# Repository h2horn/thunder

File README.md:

Lightning Thunder
=================

Controlling [LPD8806](https://www.adafruit.com/products/306) based LED Strips over Network.

* control up to 4 LPD8806 based LED Strips
* simple UDP Protocol

Components
----------

Based on:

* [ATxmega16A4](http://www.atmel.com/Images/Atmel-8331-8-and-16-bit-AVR-Microcontroller-XMEGA-AU_Manual.pdf) - Low power, high performance 8/16-bit AVR microcontroller
* [ENC28J60](http://ww1.microchip.com/downloads/en/DeviceDoc/39662e.pdf) - Microchip 10Mbit Ethernet controller with SPI interface

Protocol
--------

`Thunder` recieves UDP data containing the raw LPD8806 data for each Strip
on seperate UDP Ports (50000-50003). It forwards the data directly over SPI, without any checking or modification.

The Host has full control and has to calculate the correct order and
color ordering (RBG -> RGB), etc...

Result
------

LICENSE
-------

Released under the [MIT](http://opensource.org/licenses/MIT) License.
Based on the [Open Source Hardware Definition v1.0](http://www.oshwa.org/definition/).

See the respective source code files for varying Licenses.

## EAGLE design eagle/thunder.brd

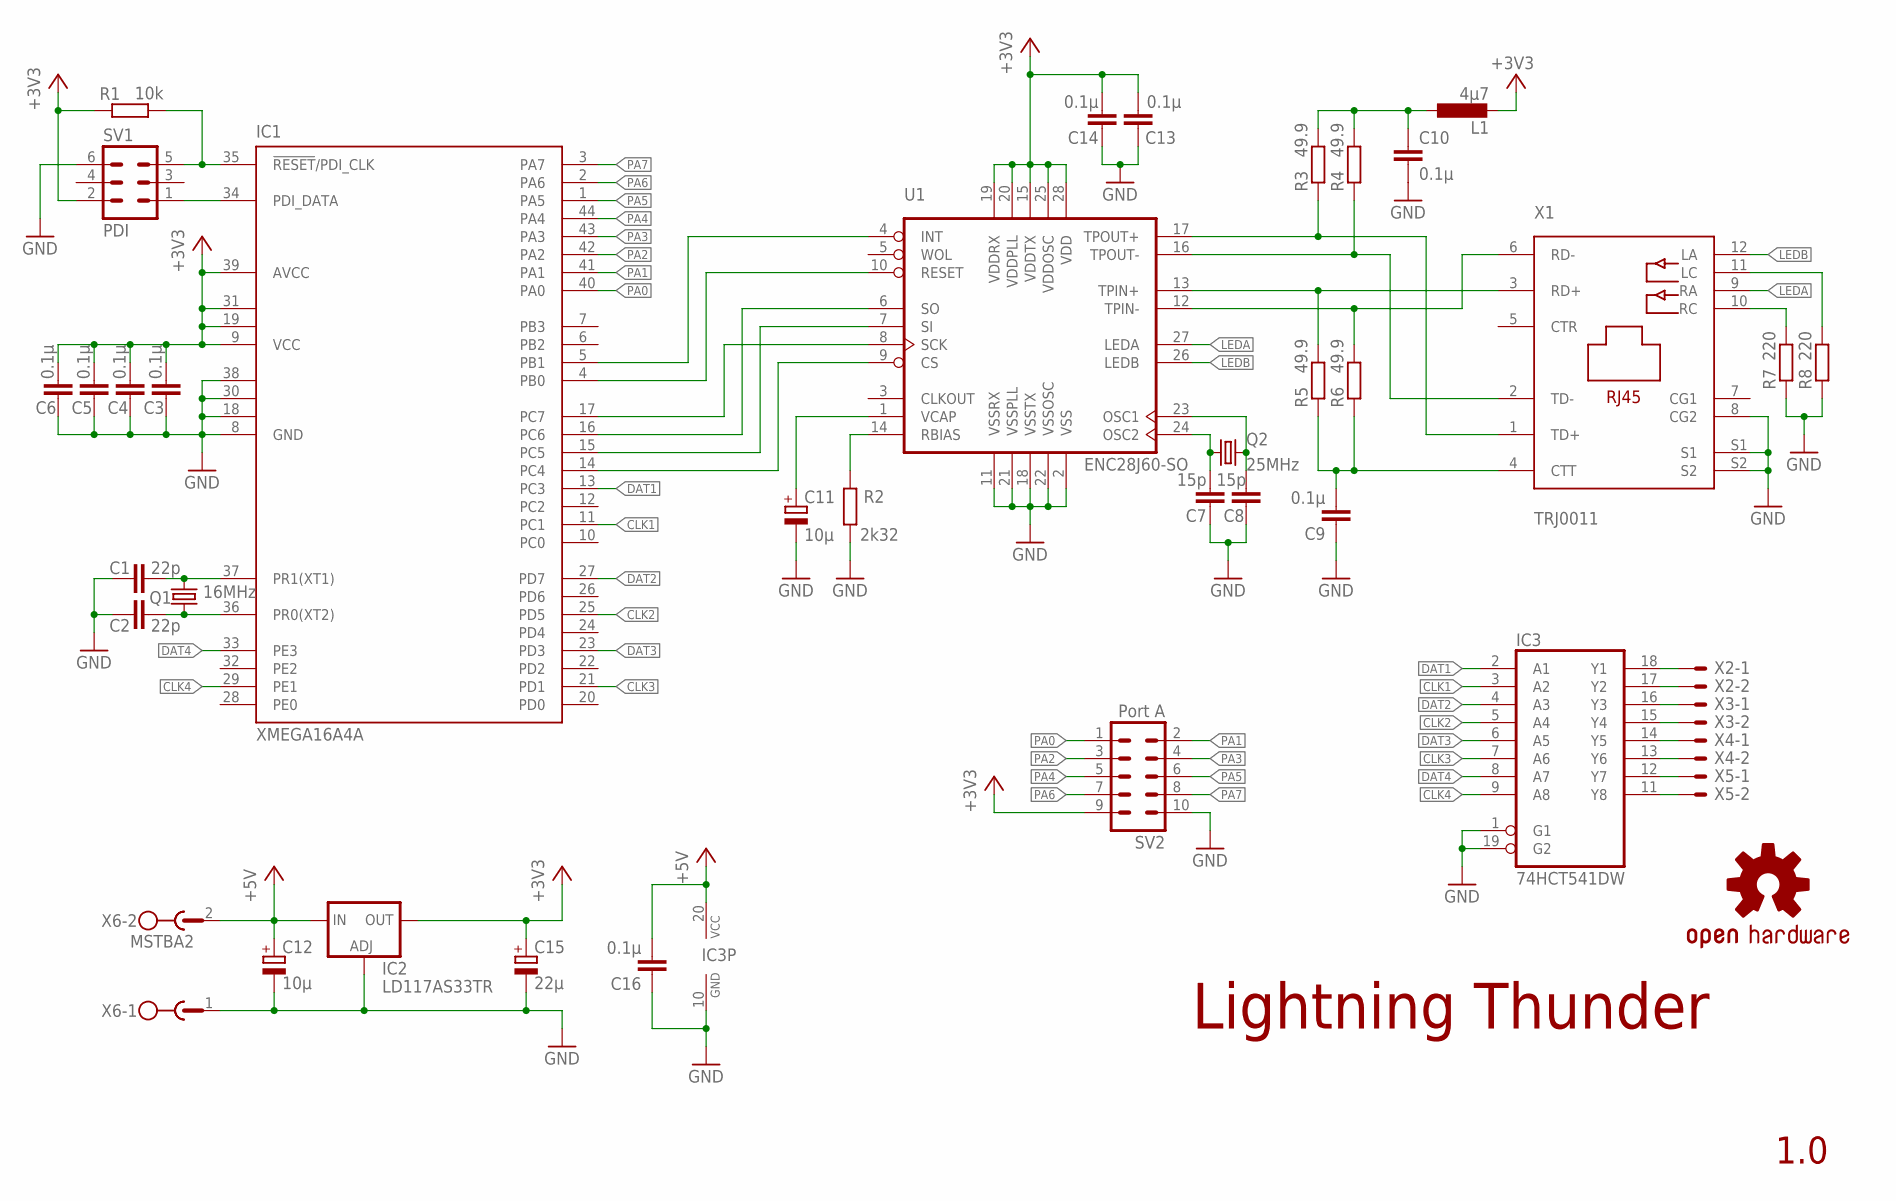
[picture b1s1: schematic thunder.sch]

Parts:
C1, C2: 22p; C0805
C3, C4, C5, C6, C9, C10, C13, C14, C16: 0.1µ; C0805
C7, C8: 15p; C0805
C11, C12: 10µ; B/3528-21R
C15: 22µ; B/3528-21R
IC1: XMEGA16A4A; TQFP44
IC2: LD117AS33TR; SOT223
IC3: 74HCT541DW; SO20W
L1: 4µ7; L3225M
LOGO1: OSHW-LOGOS; OSHW-LOGO-S
Q1: 16MHz; HC49U-V
Q2: 25MHz; HC49U-V
R1: 10k; R0805
R2: 2k32; R0805
R3, R4, R5, R6: 49.9; R0805
R7, R8: 220; R0805
SV1: PDI; ML6
SV2: Port A; MA05-2
U1: ENC28J60-SO; SO28W
X1: TRJ0011
X2, X3, X4, X5: AKL18X-02W; AKL182-02
X6: MSTBA2

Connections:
+3V3: C3.2, C4.2, C5.2, C6.2, C13.2, C14.2, C15.+, IC1.9 (VCC), IC1.19 (VCC1), IC1.31 (VCC2), IC1.39 (AVCC), IC2.4 (OUT), L1.2, R1.2, SV1.2, SV2.9, U1.15 (VDDTX), U1.19 (VDDRX), U1.20 (VDDPLL), U1.25 (VDDOSC), U1.28 (VDD)
+5V: C12.+, C16.2, IC2.3 (IN), IC3.20 (VCC), X6.2
CLK1: IC1.11 (PC1), IC3.3 (A2)
CLK2: IC1.25 (PD5), IC3.5 (A4)
CLK3: IC1.21 (PD1), IC3.7 (A6)
CLK4: IC1.29 (PE1), IC3.9 (A8)
DAT1: IC1.13 (PC3), IC3.2 (A1)
DAT2: IC1.27 (PD7), IC3.4 (A3)
DAT3: IC1.23 (PD3), IC3.6 (A5)
DAT4: IC1.33 (PE3), IC3.8 (A7)
GND: C1.1, C2.1, C3.1, C4.1, C5.1, C6.1, C7.1, C8.1, C9.1, C10.2, C11.-, C12.-, C13.1, C14.1, C15.-, C16.1, IC1.8 (GND), IC1.18 (GND1), IC1.30 (GND2), IC1.38 (GND3), IC2.1 (ADJ), IC3.1 (G1), IC3.10 (GND), IC3.19 (G2), R2.1, R7.1, R8.1, SV1.6, SV2.10, U1.2 (VSS), U1.11 (VSSRX), U1.18 (VSSTX), U1.21 (VSSPLL), U1.22 (VSSOSC), X1.8 (CG2), X1.S1, X1.S2, X6.1
LEDA: U1.27 (LEDA), X1.9 (RA)
LEDB: U1.26 (LEDB), X1.12 (LA)
unnamed: IC1.34 (PDI_DATA), SV1.1
unnamed: IC1.35 (!RESET!/PDI_CLK), R1.1, SV1.5
unnamed: C2.2, IC1.36 (PR0(XT2)), Q1.1
unnamed: C1.2, IC1.37 (PR1(XT1)), Q1.2
unnamed: IC1.14 (PC4), U1.9 (CS)
unnamed: IC1.17 (PC7), U1.8 (SCK)
unnamed: IC1.16 (PC6), U1.6 (SO)
unnamed: IC1.15 (PC5), U1.7 (SI)
unnamed: IC1.4 (PB0), U1.10 (RESET)
unnamed: IC1.5 (PB1), U1.4 (INT)
unnamed: R3.1, U1.17 (TPOUT+), X1.1 (TD+)
unnamed: R4.1, U1.16 (TPOUT-), X1.2 (TD-)
unnamed: R5.2, U1.13 (TPIN+), X1.3 (RD+)
unnamed: R6.2, U1.12 (TPIN-), X1.6 (RD-)
unnamed: R2.2, U1.14 (RBIAS)
unnamed: C10.1, L1.1, R3.2, R4.2
unnamed: C9.2, R5.1, R6.1, X1.4 (CTT)
unnamed: C11.+, U1.1 (VCAP)
unnamed: IC3.18 (Y1), X2.P$1
unnamed: C7.2, Q2.1, U1.24 (OSC2)
unnamed: C8.2, Q2.2, U1.23 (OSC1)
unnamed: IC3.17 (Y2), X2.P$2
unnamed: IC3.16 (Y3), X3.P$1
unnamed: IC3.15 (Y4), X3.P$2
unnamed: R7.2, X1.10 (RC)
unnamed: R8.2, X1.11 (LC)
unnamed: IC3.14 (Y5), X4.P$1
unnamed: IC3.13 (Y6), X4.P$2
unnamed: IC3.12 (Y7), X5.P$1
unnamed: IC3.11 (Y8), X5.P$2
PA0: IC1.40 (PA0), SV2.1
PA1: IC1.41 (PA1), SV2.2
PA2: IC1.42 (PA2), SV2.3
PA3: IC1.43 (PA3), SV2.4
PA4: IC1.44 (PA4), SV2.5
PA5: IC1.1 (PA5), SV2.6
PA6: IC1.2 (PA6), SV2.7
PA7: IC1.3 (PA7), SV2.8

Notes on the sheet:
Lightning Thunder
1.0

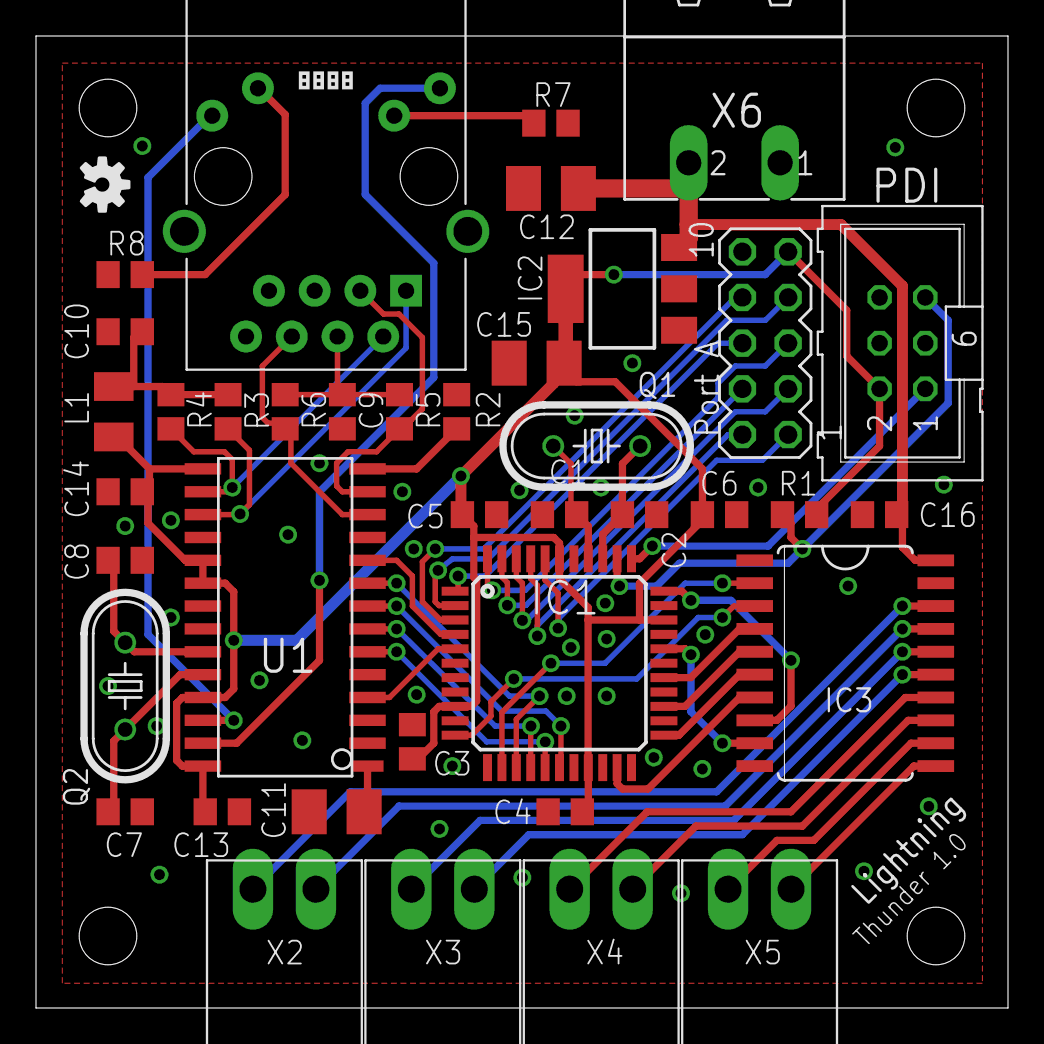
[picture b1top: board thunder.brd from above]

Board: 2 copper layers, 54.0 x 54.0 mm, 41 parts (0 on the bottom side), 51 nets.

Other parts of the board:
U$1: LP_NUMBER_SILK_TOP

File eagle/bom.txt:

Qty Value       Device            Package     Parts                                  Description
2   22p         C-EUC0805         C0805       C1, C2                                 CAPACITOR, European symbol
9   0.1µ        C-EUC0805         C0805       C3, C4, C5, C6, C9, C10, C13, C14, C16 CAPACITOR, European symbol
2   15p         C-EUC0805         C0805       C7, C8                                 CAPACITOR, European symbol
2   10µ         CPOL-EUB/3528-21R B/3528-21R  C11, C12                               POLARIZED CAPACITOR, European symbol
1   22µ         CPOL-EUB/3528-21R B/3528-21R  C15                                    POLARIZED CAPACITOR, European symbol
1   10k         R-EU_R0805        R0805       R1                                     RESISTOR, European symbol
2   220         R-EU_R0805        R0805       R7, R8                                 RESISTOR, European symbol
1   2k32        R-EU_R0805        R0805       R2                                     RESISTOR, European symbol
4   49.9        R-EU_R0805        R0805       R3, R4, R5, R6                         RESISTOR, European symbol
1   16MHz       CRYSTALHC49U-V    HC49U-V     Q1                                     CRYSTAL
1   25MHz       CRYSTALHC49U-V    HC49U-V     Q2                                     CRYSTAL
1   4µ7         L-EUL3225M        L3225M      L1                                     INDUCTOR, European symbol
1   XMEGA16A4A  XMEGA16A4A        TQFP44      IC1                                    MICROCONTROLLER
1   ENC28J60-SO ENC28J60-SO       SO28W       U1                                     Microchip 10Mbit Ethernet controller with SPI interface
1   LD117AS33TR LD117AS33TR       SOT223      IC2                                    Low drop fixed and adjustable positive voltage regulators 1 A
1   74HCT541DW  74HCT541DW        SO20W       IC3                                    Octal BUFFER and LINE DRIVER, 3-state
1   TRJ0011     TRJ0011           TRJ0011     X1                                     10/100Base-TX RJ45 Connector With Integrated Magnetics(Tab-Down)
4   AKL18X-02W  AKL18X-02W        AKL182-02   X2, X3, X4, X5                         Riacon AKL18X Steckverbinder
1   MSTBA2      MSTBA2            MSTBA2      X6                                     PHOENIX
1   PDI         ML6               ML6         SV1                                    HARTING
1   Port A      MA05-2            MA05-2      SV2                                    PIN HEADER

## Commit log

2014-11-15 fix README typo
2015-02-06 add closeup image

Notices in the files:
parts and their libraries:
SparkFun-Aesthetics: Licensing: Creative Commons ShareAlike 4.0 International - https://creativecommons.org/licenses/by-sa/4.0
